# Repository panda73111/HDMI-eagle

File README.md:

[pandaLight on 3D Warehouse](https://3dwarehouse.sketchup.com/model.html?id=u218e26f0-69cc-4069-a915-63719f472bee)

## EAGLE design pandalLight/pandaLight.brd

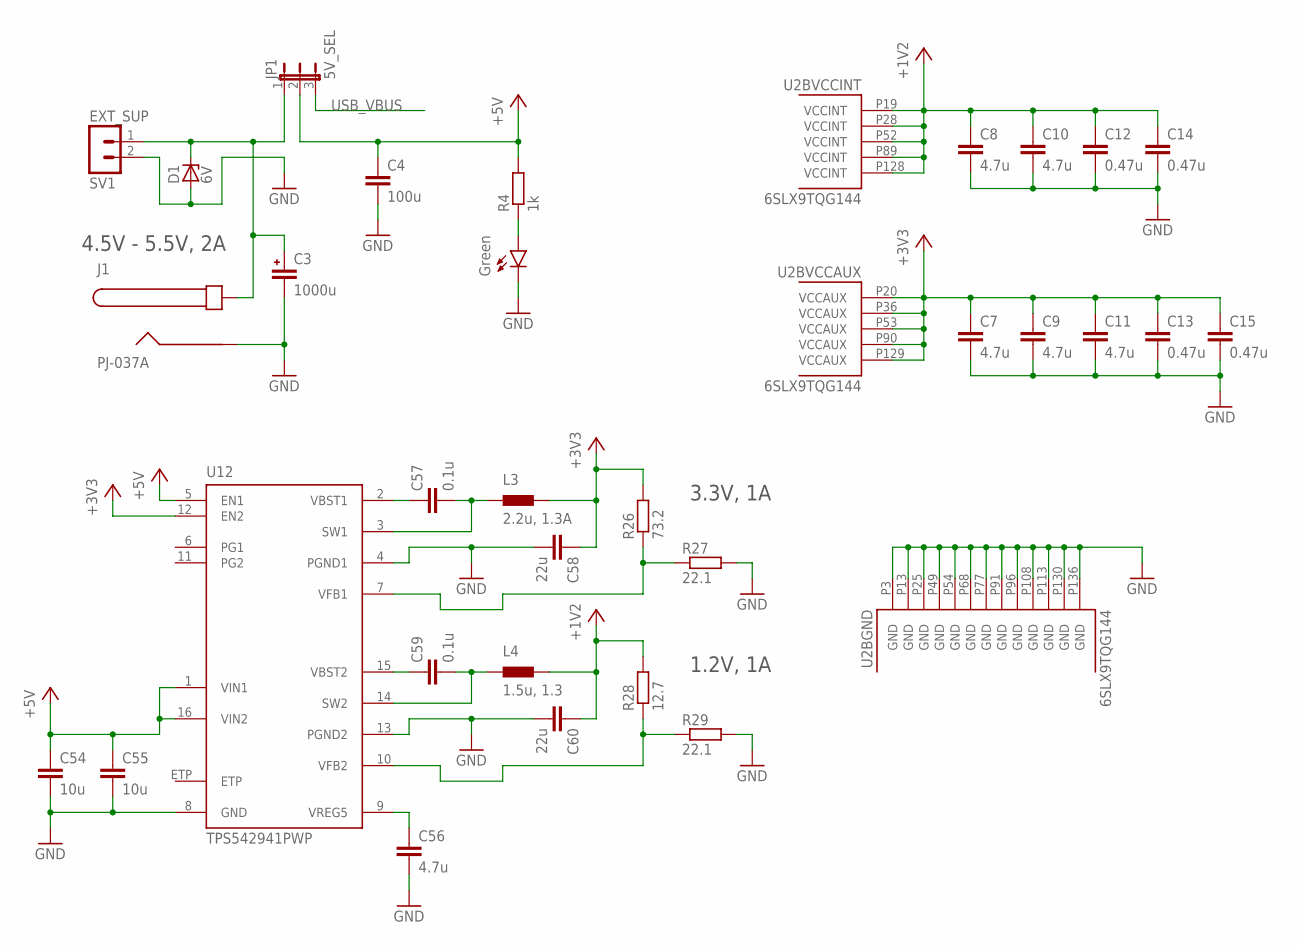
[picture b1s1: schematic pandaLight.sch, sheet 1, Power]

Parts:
C3: 1000u; MVY_HA0; PARTNO EMVY6R3ADA102MHA0G
C4: 100u; C1206; PARTNO CL31A107MQHNNNE
C7, C8, C9, C10, C11, C56: 4.7u; C0603; PARTNO C0603C475K9PACTU
C12, C13, C14, C15: 0.47u; C0402; PARTNO C1005X5R0J474K050BB
C54, C55: 10u; C0603; PARTNO CL10A106MQ8NNNC
C57, C59: 0.1u; C0402; PARTNO CL05B104KP5NNNC
C58, C60: 22u; C0603; PARTNO CL10A226MQ8NRNC
D1: 6V; DO-214AC; PARTNO SMAJ6.0A
J1: PJ-037A; PARTNO PJ-037A
JP1: 5V_SEL; JP2; PARTNO SPC02SYAN
L3: 2.2u, 1.3A; SRN3015_3X3; PARTNO SRN3015-2R2M
L4: 1.5u, 1.3; SRN3015_3X3; PARTNO SRN3015-1R5Y
LED1: Green; LED-0603; PARTNO LTST-C191KGKT
R4: 1k; R0402; PARTNO ERJ-2RKF1001X
R26: 73.2; R0402; PARTNO ERJ-2RKF73R2X
R27, R29: 22.1; R0402; PARTNO ERJ-2RKF22R1X
R28: 12.7; R0402; PARTNO ERJ-2RKF12R7X
SV1: EXT_SUP; MA02-1; PARTNO *
U2: 6SLX9TQG144; TQ144; PARTNO XC6SLX9-3TQG144C
U12: TPS542941PWP; R-PDSO-G16; PARTNO TPS542941PWP

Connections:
5V_SUP: C3.1, D1.C, J1.CENTER, JP1.1, SV1.1; also elsewhere on the board
+1V2: C8.1, C10.1, C12.1, C14.1, C60.1, L4.2, R28.2, U2.P19 (VCCINT), U2.P28 (VCCINT), U2.P52 (VCCINT), U2.P89 (VCCINT), U2.P128 (VCCINT)
+3V3: C7.1, C9.1, C11.1, C13.1, C15.1, C58.1, L3.2, R26.2, U2.P20 (VCCAUX), U2.P36 (VCCAUX), U2.P53 (VCCAUX), U2.P90 (VCCAUX), U2.P129 (VCCAUX), U12.12 (EN2); also elsewhere on the board
+5V: C4.1, C54.1, C55.1, JP1.2, R4.2, U12.1 (VIN1), U12.5 (EN1), U12.16 (VIN2); also elsewhere on the board
GND: C3.2, C4.2, C7.2, C8.2, C9.2, C10.2, C11.2, C12.2, C13.2, C14.2, C15.2, C54.2, C55.2, C56.2, C58.2, C60.2, D1.A, J1.BARREL, LED1.C, R27.2, R29.2, SV1.2, U2.P3 (GND), U2.P13 (GND), U2.P25 (GND), U2.P49 (GND), U2.P54 (GND), U2.P68 (GND), U2.P77 (GND), U2.P91 (GND), U2.P96 (GND), U2.P108 (GND), U2.P113 (GND), U2.P130 (GND), U2.P136 (GND), U12.4 (PGND1), U12.8 (GND), U12.13 (PGND2); also elsewhere on the board
unnamed: C57.2, L3.1, U12.3 (SW1)
unnamed: R26.1, R27.1, U12.7 (VFB1)
unnamed: C57.1, U12.2 (VBST1)
unnamed: R28.1, R29.1, U12.10 (VFB2)
unnamed: C59.1, U12.15 (VBST2)
unnamed: C59.2, L4.1, U12.14 (SW2)
unnamed: LED1.A, R4.1
USB_VBUS: JP1.3; also elsewhere on the board
VREG5: C56.1, U12.9 (VREG5)

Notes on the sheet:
4.5V - 5.5V, 2A
3.3V, 1A
1.2V, 1A

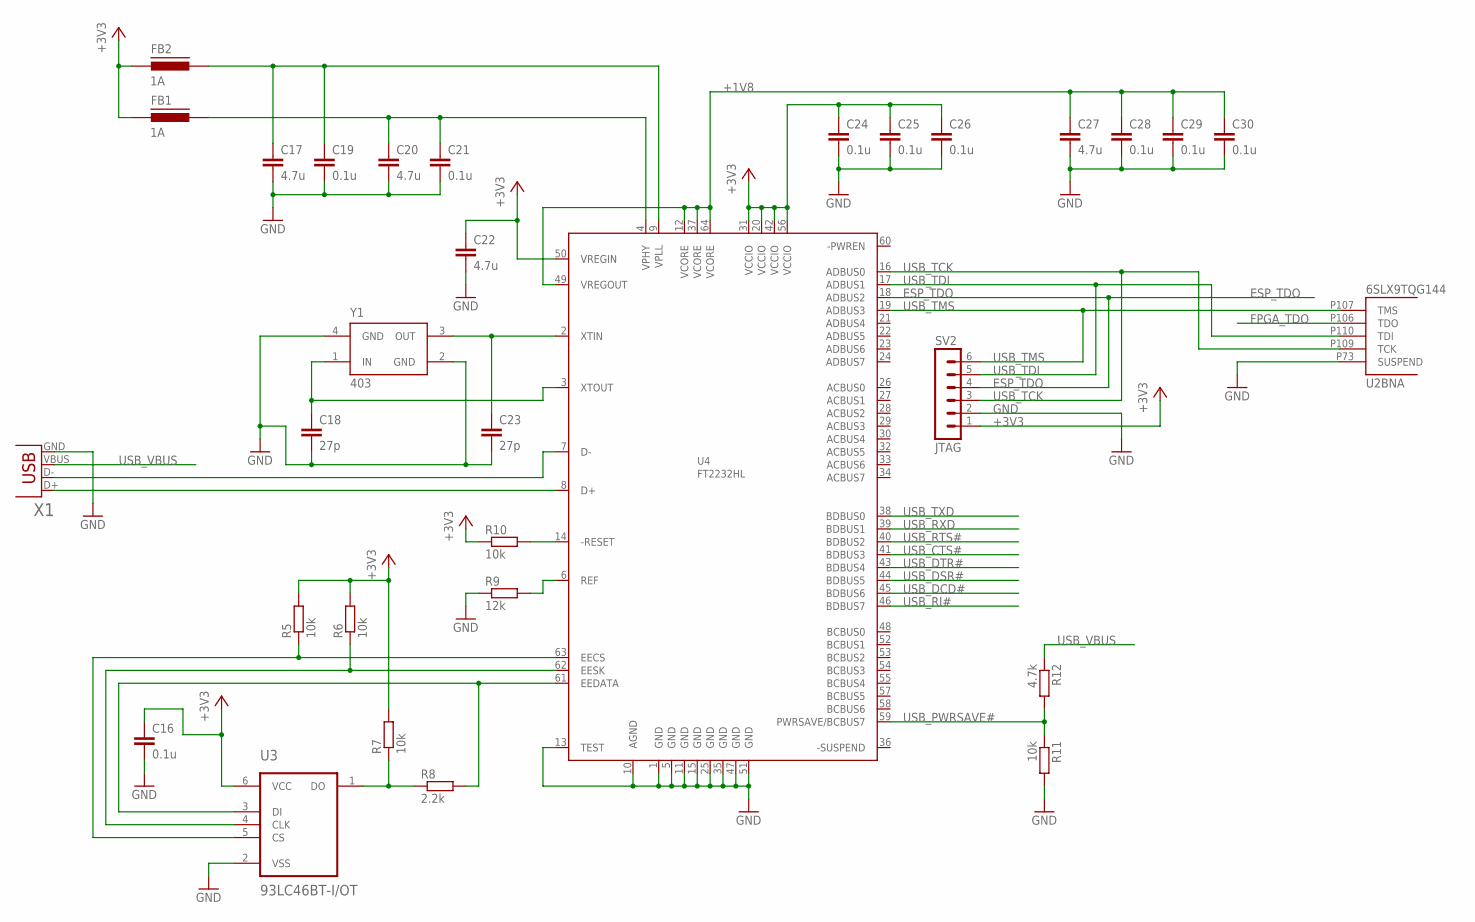
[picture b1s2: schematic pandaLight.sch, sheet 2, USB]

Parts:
C16, C19, C21, C24, C25, C26, C28, C29, C30: 0.1u; C0402; PARTNO CL05B104KP5NNNC
C17, C20, C22, C27: 4.7u; C0603; PARTNO C0603C475K9PACTU
C18, C23: 27p; C0402; PARTNO CL05C270JB5NNNC
FB1, FB2: 1A; FB0402; PARTNO BK1005HS100-T
R5, R6, R7, R10, R11: 10k; R0402; PARTNO ERJ-2RKF1002X
R8: 2.2k; R0402; PARTNO ERJ-2RKF2201X
R9: 12k; R0402; PARTNO ERJ-2RKF1202X
R12: 4.7k; R0402; PARTNO ERJ-2RKF4701X
SV2: JTAG; MA06-1; PARTNO *
U2: 6SLX9TQG144; TQ144; PARTNO XC6SLX9-3TQG144C
U3: 93LC46BT-I/OT; SOT23-6; PARTNO 93LC46BT-I/OT
U4: FT2232HL; LQFP64; PARTNO FT2232HL-REEL
X1: USBUB-S; USB-UB-S; PARTNO 10118192-0001LF
Y1: 403; 403-3.2X2.5; PARTNO 403C35D12M00000

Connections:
+1V8: C27.1, C28.1, C29.1, C30.1, U4.12 (VCORE), U4.37 (VCORE), U4.49 (VREGOUT), U4.64 (VCORE)
+3V3: C16.1, C22.1, C24.1, C25.1, C26.1, FB1.1, FB2.1, R5.2, R6.2, R7.2, R10.1, SV2.1, U3.6 (VCC), U4.20 (VCCIO), U4.31 (VCCIO), U4.42 (VCCIO), U4.50 (VREGIN), U4.56 (VCCIO); also elsewhere on the board
ESP_TDO: SV2.4, U4.18 (ADBUS2); also elsewhere on the board
FPGA_TDO: U2.P106 (TDO); also elsewhere on the board
GND: C16.2, C17.2, C18.2, C19.2, C20.2, C21.2, C22.2, C23.2, C24.2, C25.2, C26.2, C27.2, C28.2, C29.2, C30.2, R9.1, R11.2, SV2.2, U2.P73 (SUSPEND), U3.2 (VSS), U4.1 (GND), U4.5 (GND), U4.10 (AGND), U4.11 (GND), U4.13 (TEST), U4.15 (GND), U4.25 (GND), U4.35 (GND), U4.47 (GND), U4.51 (GND), X1.GND, Y1.2 (GND), Y1.4 (GND); also elsewhere on the board
unnamed: C23.1, U4.2 (XTIN), Y1.3 (OUT)
unnamed: C18.1, U4.3 (XTOUT), Y1.1 (IN)
unnamed: R5.1, U3.5 (CS), U4.63 (EECS)
unnamed: U4.7 (D-), X1.D-
unnamed: U4.8 (D+), X1.D+
unnamed: R6.1, U3.4 (CLK), U4.62 (EESK)
unnamed: R8.2, U3.3 (DI), U4.61 (EEDATA)
unnamed: R9.2, U4.6 (REF)
unnamed: R7.1, R8.1, U3.1 (DO)
unnamed: R10.2, U4.14 (-RESET)
unnamed: C20.1, C21.1, FB1.2, U4.4 (VPHY)
unnamed: C17.1, C19.1, FB2.2, U4.9 (VPLL)
USB_CTS#: U4.41 (BDBUS3); also elsewhere on the board
USB_DCD#: U4.45 (BDBUS6); also elsewhere on the board
USB_DSR#: U4.44 (BDBUS5); also elsewhere on the board
USB_DTR#: U4.43 (BDBUS4); also elsewhere on the board
USB_PWRSAVE#: R11.1, R12.2, U4.59 (PWRSAVE/BCBUS7)
USB_RI#: U4.46 (BDBUS7); also elsewhere on the board
USB_RTS#: U4.40 (BDBUS2); also elsewhere on the board
USB_RXD: U4.39 (BDBUS1); also elsewhere on the board
USB_TCK: SV2.3, U2.P109 (TCK), U4.16 (ADBUS0); also elsewhere on the board
USB_TDI: SV2.5, U2.P110 (TDI), U4.17 (ADBUS1)
USB_TMS: SV2.6, U2.P107 (TMS), U4.19 (ADBUS3); also elsewhere on the board
USB_TXD: U4.38 (BDBUS0); also elsewhere on the board
USB_VBUS: R12.1, X1.VBUS; also elsewhere on the board

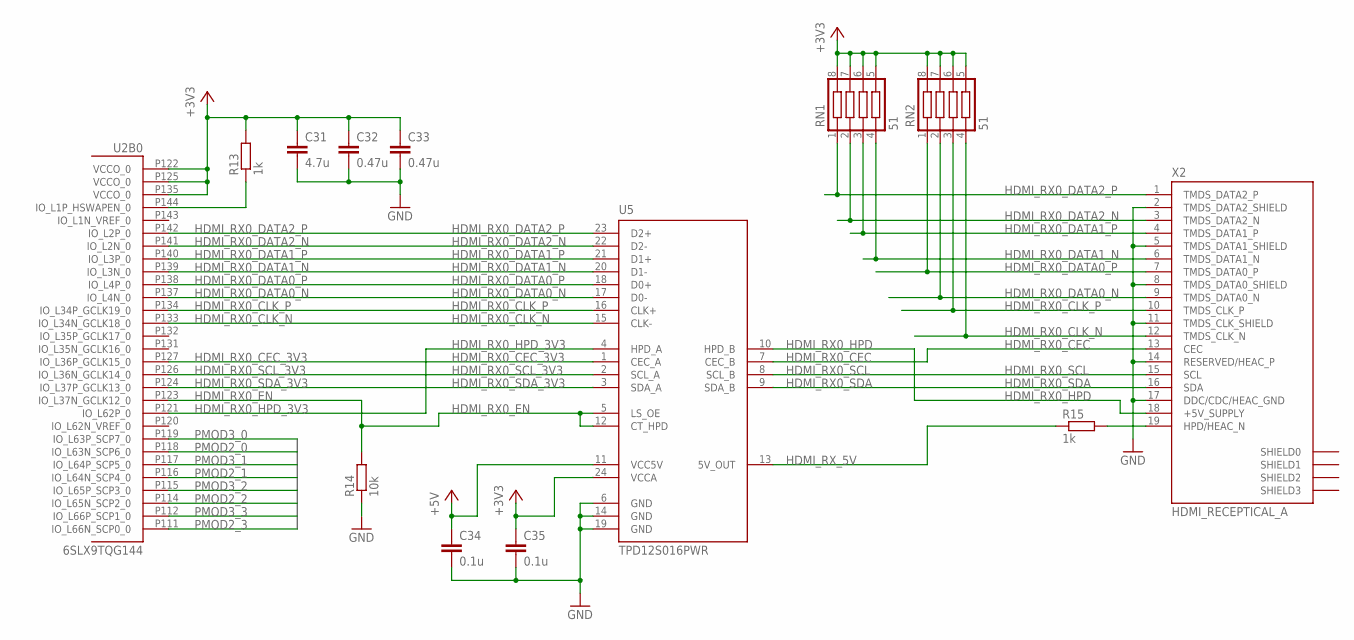
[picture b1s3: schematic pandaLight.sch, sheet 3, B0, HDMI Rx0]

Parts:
C31: 4.7u; C0603; PARTNO C0603C475K9PACTU
C32, C33: 0.47u; C0402; PARTNO C1005X5R0J474K050BB
C34, C35: 0.1u; C0402; PARTNO CL05B104KP5NNNC
R13, R15: 1k; R0402; PARTNO ERJ-2RKF1001X
R14: 10k; R0402; PARTNO ERJ-2RKF1002X
RN1, RN2: 51; 741C083; PARTNO 741C083510JP
U2: 6SLX9TQG144; TQ144; PARTNO XC6SLX9-3TQG144C
U5: TPD12S016PWR; PW_R-PDSO-G24; PARTNO TPD12S016PWR
X2: HDMI_RECEPTICAL_A; HDMI_TYPE_A_RECEPTICAL; PARTNO 10029449-111RLF

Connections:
+3V3: C31.1, C32.1, C33.1, C35.1, R13.2, RN1.5, RN1.6, RN1.7, RN1.8, RN2.5, RN2.6, RN2.7, RN2.8, U2.P122 (VCCO_0), U2.P125 (VCCO_0), U2.P135 (VCCO_0), U5.24 (VCCA); also elsewhere on the board
+5V: C34.1, U5.11 (VCC5V); also elsewhere on the board
GND: C31.2, C32.2, C33.2, C34.2, C35.2, R14.1, U5.6 (GND), U5.14 (GND), U5.19 (GND), X2.2 (TMDS_DATA2_SHIELD), X2.5 (TMDS_DATA1_SHIELD), X2.8 (TMDS_DATA0_SHIELD), X2.11 (TMDS_CLK_SHIELD), X2.14 (RESERVED/HEAC_P), X2.17 (DDC/CDC/HEAC_GND); also elsewhere on the board
HDMI_RX0_CEC: U5.7 (CEC_B), X2.13 (CEC)
HDMI_RX0_CEC_3V3: U2.P127 (IO_L36P_GCLK15_0), U5.1 (CEC_A)
HDMI_RX0_CLK_N: RN2.4, U2.P133 (IO_L34N_GCLK18_0), U5.15 (CLK-), X2.12 (TMDS_CLK_N)
HDMI_RX0_CLK_P: RN2.3, U2.P134 (IO_L34P_GCLK19_0), U5.16 (CLK+), X2.10 (TMDS_CLK_P)
HDMI_RX0_DATA0_N: RN2.2, U2.P137 (IO_L4N_0), U5.17 (D0-), X2.9 (TMDS_DATA0_N)
HDMI_RX0_DATA0_P: RN2.1, U2.P138 (IO_L4P_0), U5.18 (D0+), X2.7 (TMDS_DATA0_P)
HDMI_RX0_DATA1_N: RN1.4, U2.P139 (IO_L3N_0), U5.20 (D1-), X2.6 (TMDS_DATA1_N)
HDMI_RX0_DATA1_P: RN1.3, U2.P140 (IO_L3P_0), U5.21 (D1+), X2.4 (TMDS_DATA1_P)
HDMI_RX0_DATA2_N: RN1.2, U2.P141 (IO_L2N_0), U5.22 (D2-), X2.3 (TMDS_DATA2_N)
HDMI_RX0_DATA2_P: RN1.1, U2.P142 (IO_L2P_0), U5.23 (D2+), X2.1 (TMDS_DATA2_P)
HDMI_RX0_EN: R14.2, U2.P123 (IO_L37N_GCLK12_0), U5.5 (LS_OE), U5.12 (CT_HPD)
HDMI_RX0_HPD: U5.10 (HPD_B), X2.18 (+5V_SUPPLY)
HDMI_RX0_HPD_3V3: U2.P121 (IO_L62P_0), U5.4 (HPD_A)
HDMI_RX0_SCL: U5.8 (SCL_B), X2.15 (SCL)
HDMI_RX0_SCL_3V3: U2.P126 (IO_L36N_GCLK14_0), U5.2 (SCL_A)
HDMI_RX0_SDA: U5.9 (SDA_B), X2.16 (SDA)
HDMI_RX0_SDA_3V3: U2.P124 (IO_L37P_GCLK13_0), U5.3 (SDA_A)
HDMI_RX_5V: R15.1, U5.13 (5V_OUT)
unnamed: R13.1, U2.P144 (IO_L1P_HSWAPEN_0)
unnamed: R15.2, X2.19 (HPD/HEAC_N)
PMOD2_0: U2.P118 (IO_L63N_SCP6_0); also elsewhere on the board
PMOD2_1: U2.P116 (IO_L64N_SCP4_0); also elsewhere on the board
PMOD2_2: U2.P114 (IO_L65N_SCP2_0); also elsewhere on the board
PMOD2_3: U2.P111 (IO_L66N_SCP0_0); also elsewhere on the board
PMOD3_0: U2.P119 (IO_L63P_SCP7_0); also elsewhere on the board
PMOD3_1: U2.P117 (IO_L64P_SCP5_0); also elsewhere on the board
PMOD3_2: U2.P115 (IO_L65P_SCP3_0); also elsewhere on the board
PMOD3_3: U2.P112 (IO_L66P_SCP1_0); also elsewhere on the board

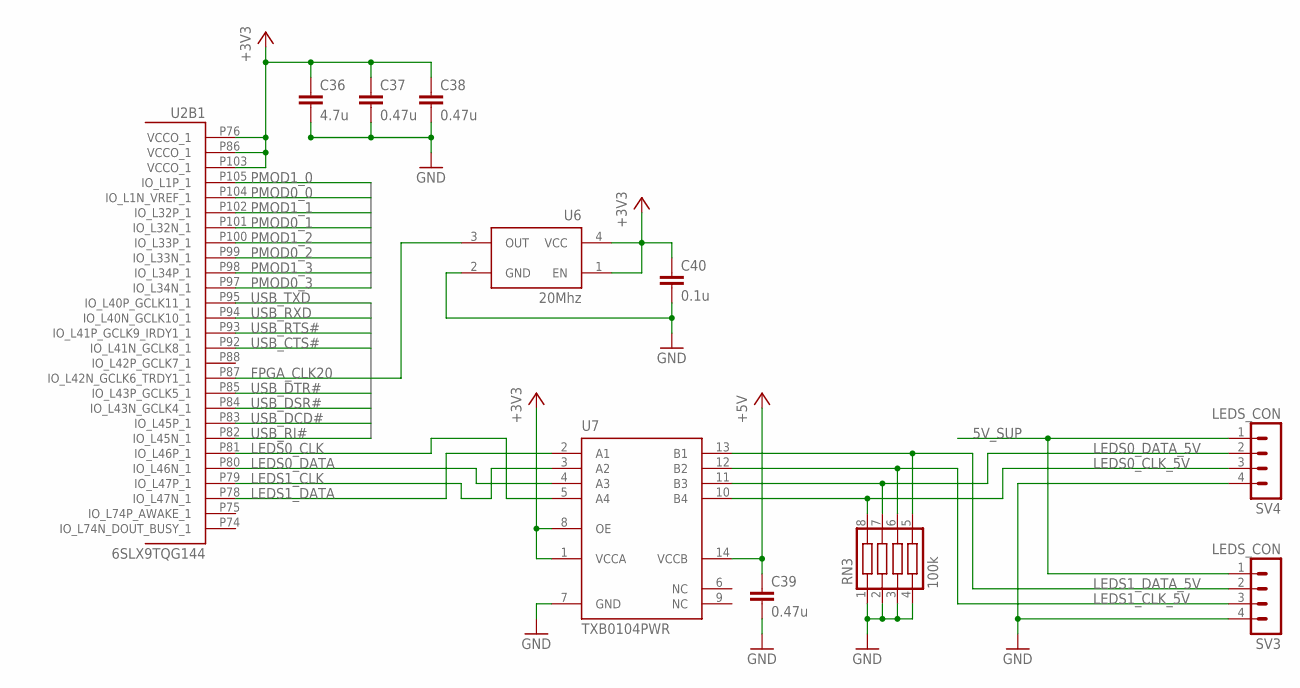
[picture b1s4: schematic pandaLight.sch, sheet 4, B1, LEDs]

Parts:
C36: 4.7u; C0603; PARTNO C0603C475K9PACTU
C37, C38, C39: 0.47u; C0402; PARTNO C1005X5R0J474K050BB
C40: 0.1u; C0402; PARTNO CL05B104KP5NNNC
RN3: 100k; 741C083; PARTNO 741C083104JP
SV3, SV4: LEDS_CON; MA04-1; PARTNO *
U2: 6SLX9TQG144; TQ144; PARTNO XC6SLX9-3TQG144C
U6: 20Mhz; OSCI-1.6X1.2; PARTNO ASCO-20.000MHZ-EK-T3
U7: TXB0104PWR; R-PDSO-G14; PARTNO TXB0104PWR

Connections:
5V_SUP: SV3.1, SV4.1; also elsewhere on the board
+3V3: C36.1, C37.1, C38.1, C40.1, U2.P76 (VCCO_1), U2.P86 (VCCO_1), U2.P103 (VCCO_1), U6.1 (EN), U6.4 (VCC), U7.1 (VCCA), U7.8 (OE); also elsewhere on the board
+5V: C39.1, U7.14 (VCCB); also elsewhere on the board
FPGA_CLK20: U2.P87 (IO_L42N_GCLK6_TRDY1_1), U6.3 (OUT)
GND: C36.2, C37.2, C38.2, C39.2, C40.2, RN3.1, RN3.2, RN3.3, RN3.4, SV3.4, SV4.4, U6.2 (GND), U7.7 (GND); also elsewhere on the board
LEDS0_CLK: U2.P81 (IO_L46P_1), U7.5 (A4)
LEDS0_CLK_5V: RN3.8, SV4.3, U7.10 (B4)
LEDS0_DATA: U2.P80 (IO_L46N_1), U7.4 (A3)
LEDS0_DATA_5V: RN3.7, SV4.2, U7.11 (B3)
LEDS1_CLK: U2.P79 (IO_L47P_1), U7.3 (A2)
LEDS1_CLK_5V: RN3.6, SV3.3, U7.12 (B2)
LEDS1_DATA: U2.P78 (IO_L47N_1), U7.2 (A1)
LEDS1_DATA_5V: RN3.5, SV3.2, U7.13 (B1)
PMOD0_0: U2.P104 (IO_L1N_VREF_1); also elsewhere on the board
PMOD0_1: U2.P101 (IO_L32N_1); also elsewhere on the board
PMOD0_2: U2.P99 (IO_L33N_1); also elsewhere on the board
PMOD0_3: U2.P97 (IO_L34N_1); also elsewhere on the board
PMOD1_0: U2.P105 (IO_L1P_1); also elsewhere on the board
PMOD1_1: U2.P102 (IO_L32P_1); also elsewhere on the board
PMOD1_2: U2.P100 (IO_L33P_1); also elsewhere on the board
PMOD1_3: U2.P98 (IO_L34P_1); also elsewhere on the board
USB_CTS#: U2.P92 (IO_L41N_GCLK8_1); also elsewhere on the board
USB_DCD#: U2.P83 (IO_L45P_1); also elsewhere on the board
USB_DSR#: U2.P84 (IO_L43N_GCLK4_1); also elsewhere on the board
USB_DTR#: U2.P85 (IO_L43P_GCLK5_1); also elsewhere on the board
USB_RI#: U2.P82 (IO_L45N_1); also elsewhere on the board
USB_RTS#: U2.P93 (IO_L41P_GCLK9_IRDY1_1); also elsewhere on the board
USB_RXD: U2.P94 (IO_L40N_GCLK10_1); also elsewhere on the board
USB_TXD: U2.P95 (IO_L40P_GCLK11_1); also elsewhere on the board

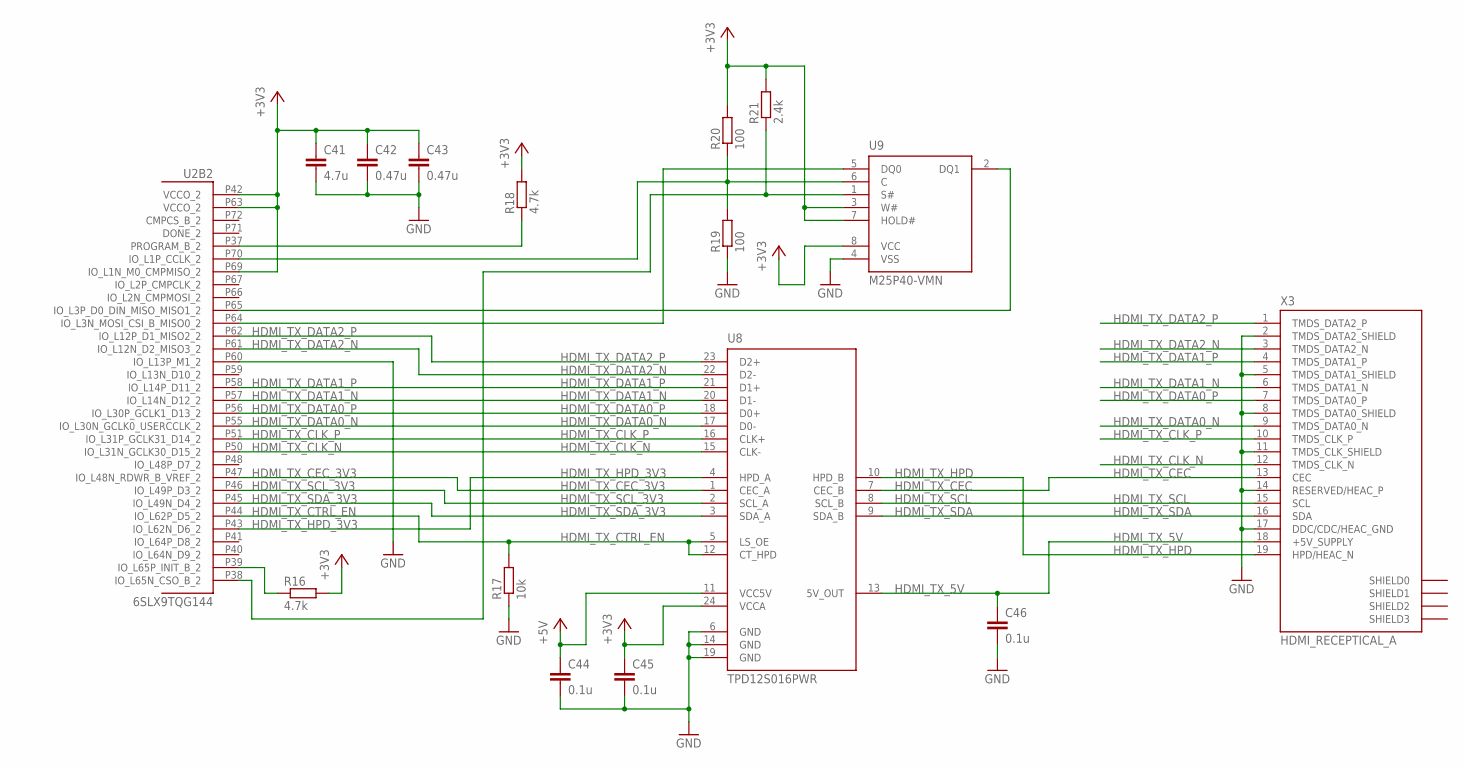
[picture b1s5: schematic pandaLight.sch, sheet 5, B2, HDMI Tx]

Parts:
C41: 4.7u; C0603; PARTNO C0603C475K9PACTU
C42, C43: 0.47u; C0402; PARTNO C1005X5R0J474K050BB
C44, C45, C46: 0.1u; C0402; PARTNO CL05B104KP5NNNC
R16, R18: 4.7k; R0402; PARTNO ERJ-2RKF4701X
R17: 10k; R0402; PARTNO ERJ-2RKF1002X
R19, R20: 100; R0402; PARTNO ERJ-2GEJ101X
R21: 2.4k; R0402; PARTNO ERJ-2RKF2401X
U2: 6SLX9TQG144; TQ144; PARTNO XC6SLX9-3TQG144C
U8: TPD12S016PWR; PW_R-PDSO-G24; PARTNO TPD12S016PWR
U9: M25P40-VMN; SO8N; PARTNO M25P80-VMN6TP
X3: HDMI_RECEPTICAL_A; HDMI_TYPE_A_RECEPTICAL; PARTNO 10029449-111RLF

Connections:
+3V3: C41.1, C42.1, C43.1, C45.1, R16.2, R18.2, R20.2, R21.2, U2.P42 (VCCO_2), U2.P63 (VCCO_2), U2.P69 (IO_L1N_M0_CMPMISO_2), U8.24 (VCCA), U9.3 (W#), U9.7 (HOLD#), U9.8 (VCC); also elsewhere on the board
+5V: C44.1, U8.11 (VCC5V); also elsewhere on the board
GND: C41.2, C42.2, C43.2, C44.2, C45.2, C46.2, R17.1, R19.1, U2.P60 (IO_L13P_M1_2), U8.6 (GND), U8.14 (GND), U8.19 (GND), U9.4 (VSS), X3.2 (TMDS_DATA2_SHIELD), X3.5 (TMDS_DATA1_SHIELD), X3.8 (TMDS_DATA0_SHIELD), X3.11 (TMDS_CLK_SHIELD), X3.14 (RESERVED/HEAC_P), X3.17 (DDC/CDC/HEAC_GND); also elsewhere on the board
HDMI_TX_5V: C46.1, U8.13 (5V_OUT), X3.18 (+5V_SUPPLY)
HDMI_TX_CEC: U8.7 (CEC_B), X3.13 (CEC)
HDMI_TX_CEC_3V3: U2.P47 (IO_L48N_RDWR_B_VREF_2), U8.1 (CEC_A)
HDMI_TX_CLK_N: U2.P50 (IO_L31N_GCLK30_D15_2), U8.15 (CLK-), X3.12 (TMDS_CLK_N)
HDMI_TX_CLK_P: U2.P51 (IO_L31P_GCLK31_D14_2), U8.16 (CLK+), X3.10 (TMDS_CLK_P)
HDMI_TX_CTRL_EN: R17.2, U2.P44 (IO_L62P_D5_2), U8.5 (LS_OE), U8.12 (CT_HPD)
HDMI_TX_DATA0_N: U2.P55 (IO_L30N_GCLK0_USERCCLK_2), U8.17 (D0-), X3.9 (TMDS_DATA0_N)
HDMI_TX_DATA0_P: U2.P56 (IO_L30P_GCLK1_D13_2), U8.18 (D0+), X3.7 (TMDS_DATA0_P)
HDMI_TX_DATA1_N: U2.P57 (IO_L14N_D12_2), U8.20 (D1-), X3.6 (TMDS_DATA1_N)
HDMI_TX_DATA1_P: U2.P58 (IO_L14P_D11_2), U8.21 (D1+), X3.4 (TMDS_DATA1_P)
HDMI_TX_DATA2_N: U2.P61 (IO_L12N_D2_MISO3_2), U8.22 (D2-), X3.3 (TMDS_DATA2_N)
HDMI_TX_DATA2_P: U2.P62 (IO_L12P_D1_MISO2_2), U8.23 (D2+), X3.1 (TMDS_DATA2_P)
HDMI_TX_HPD: U8.10 (HPD_B), X3.19 (HPD/HEAC_N)
HDMI_TX_HPD_3V3: U2.P43 (IO_L62N_D6_2), U8.4 (HPD_A)
HDMI_TX_SCL: U8.8 (SCL_B), X3.15 (SCL)
HDMI_TX_SCL_3V3: U2.P46 (IO_L49P_D3_2), U8.2 (SCL_A)
HDMI_TX_SDA: U8.9 (SDA_B), X3.16 (SDA)
HDMI_TX_SDA_3V3: U2.P45 (IO_L49N_D4_2), U8.3 (SDA_A)
unnamed: R18.1, U2.P37 (PROGRAM_B_2)
unnamed: R16.1, U2.P39 (IO_L65P_INIT_B_2)
unnamed: U2.P64 (IO_L3N_MOSI_CSI_B_MISO0_2), U9.5 (DQ0)
unnamed: R21.1, U2.P38 (IO_L65N_CSO_B_2), U9.1 (S#)
unnamed: R19.2, R20.1, U2.P70 (IO_L1P_CCLK_2), U9.6 (C)
unnamed: U2.P65 (IO_L3P_D0_DIN_MISO_MISO1_2), U9.2 (DQ1)

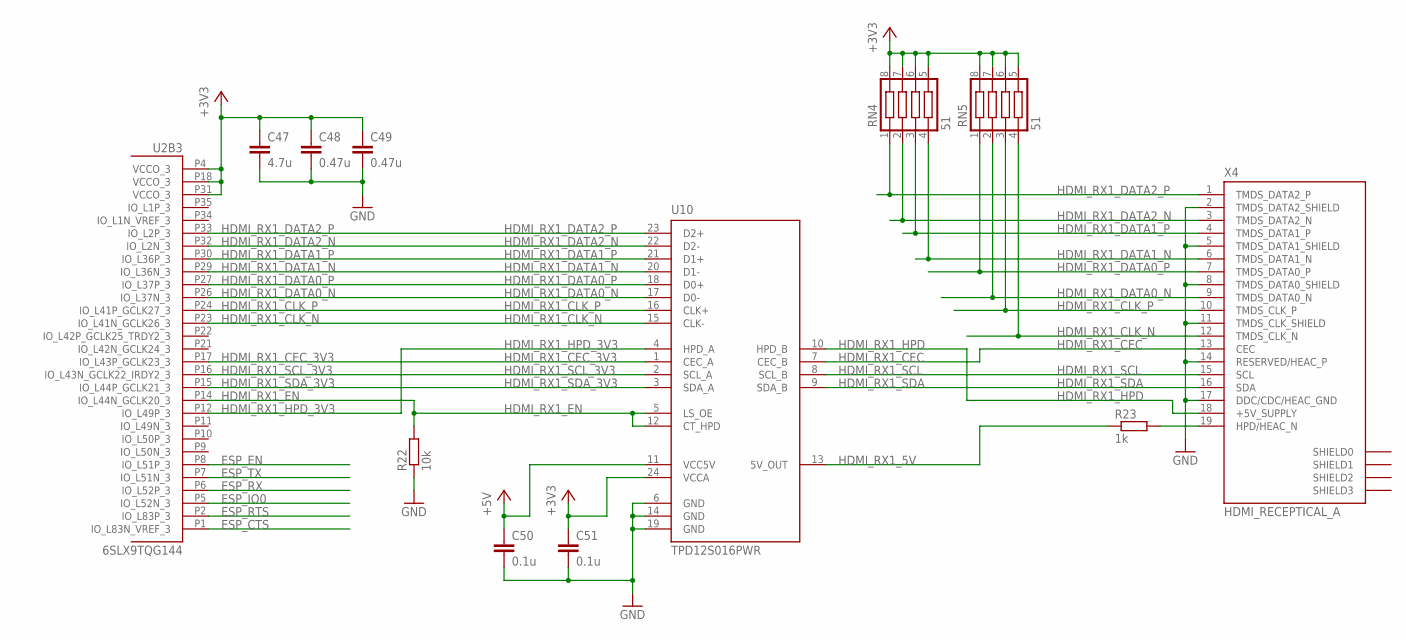
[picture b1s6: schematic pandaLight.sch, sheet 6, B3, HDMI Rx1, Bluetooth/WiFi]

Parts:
C47: 4.7u; C0603; PARTNO C0603C475K9PACTU
C48, C49: 0.47u; C0402; PARTNO C1005X5R0J474K050BB
C50, C51: 0.1u; C0402; PARTNO CL05B104KP5NNNC
R22: 10k; R0402; PARTNO ERJ-2RKF1002X
R23: 1k; R0402; PARTNO ERJ-2RKF1001X
RN4, RN5: 51; 741C083; PARTNO 741C083510JP
U2: 6SLX9TQG144; TQ144; PARTNO XC6SLX9-3TQG144C
U10: TPD12S016PWR; PW_R-PDSO-G24; PARTNO TPD12S016PWR
X4: HDMI_RECEPTICAL_A; HDMI_TYPE_A_RECEPTICAL; PARTNO 10029449-111RLF

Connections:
+3V3: C47.1, C48.1, C49.1, C51.1, RN4.5, RN4.6, RN4.7, RN4.8, RN5.5, RN5.6, RN5.7, RN5.8, U2.P4 (VCCO_3), U2.P18 (VCCO_3), U2.P31 (VCCO_3), U10.24 (VCCA); also elsewhere on the board
+5V: C50.1, U10.11 (VCC5V); also elsewhere on the board
ESP_CTS: U2.P1 (IO_L83N_VREF_3); also elsewhere on the board
ESP_EN: U2.P8 (IO_L51P_3); also elsewhere on the board
ESP_IO0: U2.P5 (IO_L52N_3); also elsewhere on the board
ESP_RTS: U2.P2 (IO_L83P_3); also elsewhere on the board
ESP_RX: U2.P6 (IO_L52P_3); also elsewhere on the board
ESP_TX: U2.P7 (IO_L51N_3); also elsewhere on the board
GND: C47.2, C48.2, C49.2, C50.2, C51.2, R22.1, U10.6 (GND), U10.14 (GND), U10.19 (GND), X4.2 (TMDS_DATA2_SHIELD), X4.5 (TMDS_DATA1_SHIELD), X4.8 (TMDS_DATA0_SHIELD), X4.11 (TMDS_CLK_SHIELD), X4.14 (RESERVED/HEAC_P), X4.17 (DDC/CDC/HEAC_GND); also elsewhere on the board
HDMI_RX1_5V: R23.1, U10.13 (5V_OUT)
HDMI_RX1_CEC: U10.7 (CEC_B), X4.13 (CEC)
HDMI_RX1_CEC_3V3: U2.P17 (IO_L43P_GCLK23_3), U10.1 (CEC_A)
HDMI_RX1_CLK_N: RN5.4, U2.P23 (IO_L41N_GCLK26_3), U10.15 (CLK-), X4.12 (TMDS_CLK_N)
HDMI_RX1_CLK_P: RN5.3, U2.P24 (IO_L41P_GCLK27_3), U10.16 (CLK+), X4.10 (TMDS_CLK_P)
HDMI_RX1_DATA0_N: RN5.2, U2.P26 (IO_L37N_3), U10.17 (D0-), X4.9 (TMDS_DATA0_N)
HDMI_RX1_DATA0_P: RN5.1, U2.P27 (IO_L37P_3), U10.18 (D0+), X4.7 (TMDS_DATA0_P)
HDMI_RX1_DATA1_N: RN4.4, U2.P29 (IO_L36N_3), U10.20 (D1-), X4.6 (TMDS_DATA1_N)
HDMI_RX1_DATA1_P: RN4.3, U2.P30 (IO_L36P_3), U10.21 (D1+), X4.4 (TMDS_DATA1_P)
HDMI_RX1_DATA2_N: RN4.2, U2.P32 (IO_L2N_3), U10.22 (D2-), X4.3 (TMDS_DATA2_N)
HDMI_RX1_DATA2_P: RN4.1, U2.P33 (IO_L2P_3), U10.23 (D2+), X4.1 (TMDS_DATA2_P)
HDMI_RX1_EN: R22.2, U2.P14 (IO_L44N_GCLK20_3), U10.5 (LS_OE), U10.12 (CT_HPD)
HDMI_RX1_HPD: U10.10 (HPD_B), X4.18 (+5V_SUPPLY)
HDMI_RX1_HPD_3V3: U2.P12 (IO_L49P_3), U10.4 (HPD_A)
HDMI_RX1_SCL: U10.8 (SCL_B), X4.15 (SCL)
HDMI_RX1_SCL_3V3: U2.P16 (IO_L43N_GCLK22_IRDY2_3), U10.2 (SCL_A)
HDMI_RX1_SDA: U10.9 (SDA_B), X4.16 (SDA)
HDMI_RX1_SDA_3V3: U2.P15 (IO_L44P_GCLK21_3), U10.3 (SDA_A)
unnamed: R23.2, X4.19 (HPD/HEAC_N)

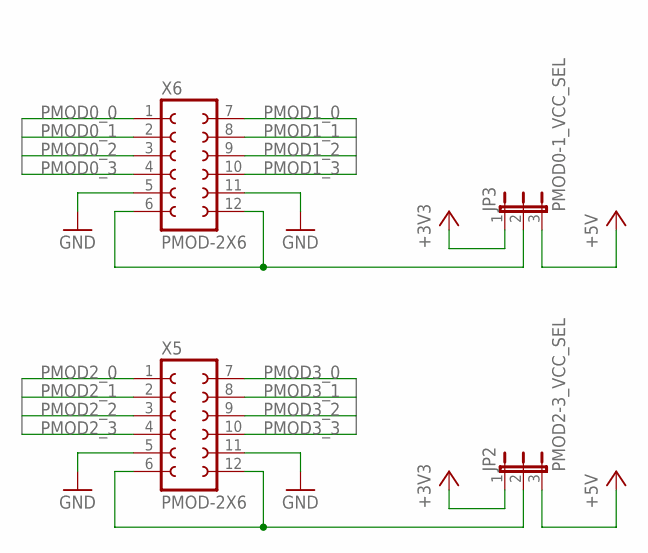
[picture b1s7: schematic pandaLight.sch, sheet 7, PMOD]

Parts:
JP2: PMOD2-3_VCC_SEL; JP2; PARTNO SPC02SYAN
JP3: PMOD0-1_VCC_SEL; JP2; PARTNO SPC02SYAN
X5, X6: PMOD-2X6; PARTNO PPTC062LJBN-RC

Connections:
+3V3: JP2.1, JP3.1; also elsewhere on the board
+5V: JP2.3, JP3.3; also elsewhere on the board
GND: X5.5, X5.11, X6.5, X6.11; also elsewhere on the board
unnamed: JP2.2, X5.6, X5.12
unnamed: JP3.2, X6.6, X6.12
PMOD0_0: X6.1; also elsewhere on the board
PMOD0_1: X6.2; also elsewhere on the board
PMOD0_2: X6.3; also elsewhere on the board
PMOD0_3: X6.4; also elsewhere on the board
PMOD1_0: X6.7; also elsewhere on the board
PMOD1_1: X6.8; also elsewhere on the board
PMOD1_2: X6.9; also elsewhere on the board
PMOD1_3: X6.10; also elsewhere on the board
PMOD2_0: X5.1; also elsewhere on the board
PMOD2_1: X5.2; also elsewhere on the board
PMOD2_2: X5.3; also elsewhere on the board
PMOD2_3: X5.4; also elsewhere on the board
PMOD3_0: X5.7; also elsewhere on the board
PMOD3_1: X5.8; also elsewhere on the board
PMOD3_2: X5.9; also elsewhere on the board
PMOD3_3: X5.10; also elsewhere on the board

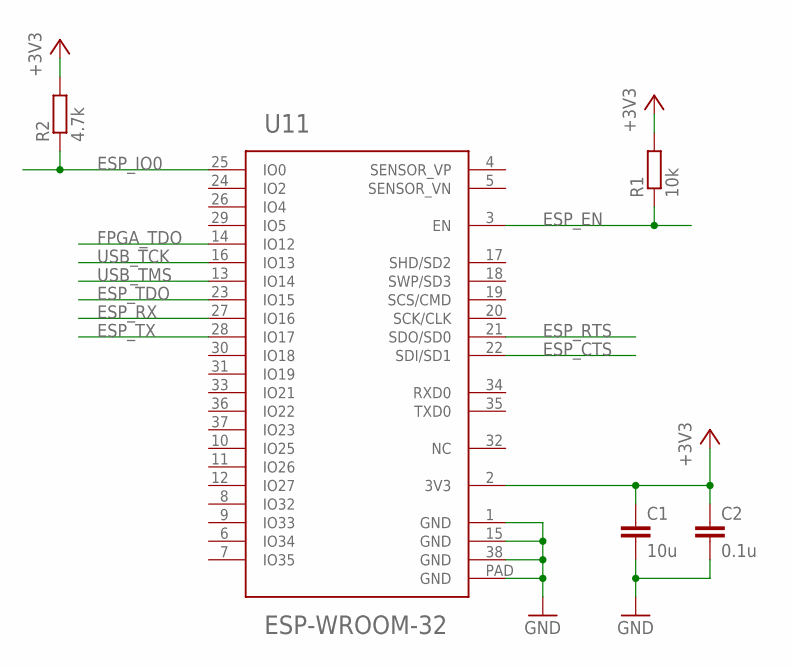
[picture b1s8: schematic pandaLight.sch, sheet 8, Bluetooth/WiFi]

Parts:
C1: 10u; C0603
C2: 0.1u; C0402; PARTNO CL05B104KP5NNNC
R1: 10k; R0402; PARTNO ERJ-2RKF1002X
R2: 4.7k; R0402; PARTNO ERJ-2RKF1002X
U11: ESP-WROOM-32

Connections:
+3V3: C1.1, C2.1, R1.2, R2.2, U11.2 (3V3); also elsewhere on the board
ESP_CTS: U11.22 (SDI/SD1); also elsewhere on the board
ESP_EN: R1.1, U11.3 (EN); also elsewhere on the board
ESP_IO0: R2.1, U11.25 (IO0); also elsewhere on the board
ESP_RTS: U11.21 (SDO/SD0); also elsewhere on the board
ESP_RX: U11.27 (IO16); also elsewhere on the board
ESP_TDO: U11.23 (IO15); also elsewhere on the board
ESP_TX: U11.28 (IO17); also elsewhere on the board
FPGA_TDO: U11.14 (IO12); also elsewhere on the board
GND: C1.2, C2.2, U11.1 (GND), U11.15 (GND), U11.38 (GND), U11.PAD (GND); also elsewhere on the board
USB_TCK: U11.16 (IO13); also elsewhere on the board
USB_TMS: U11.13 (IO14); also elsewhere on the board

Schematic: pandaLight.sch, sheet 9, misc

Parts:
FID1, FID2, FID3, FID4, FID5, FID6, FID7, FID8: FIDUCIAL1X2; FIDUCIAL-1X2

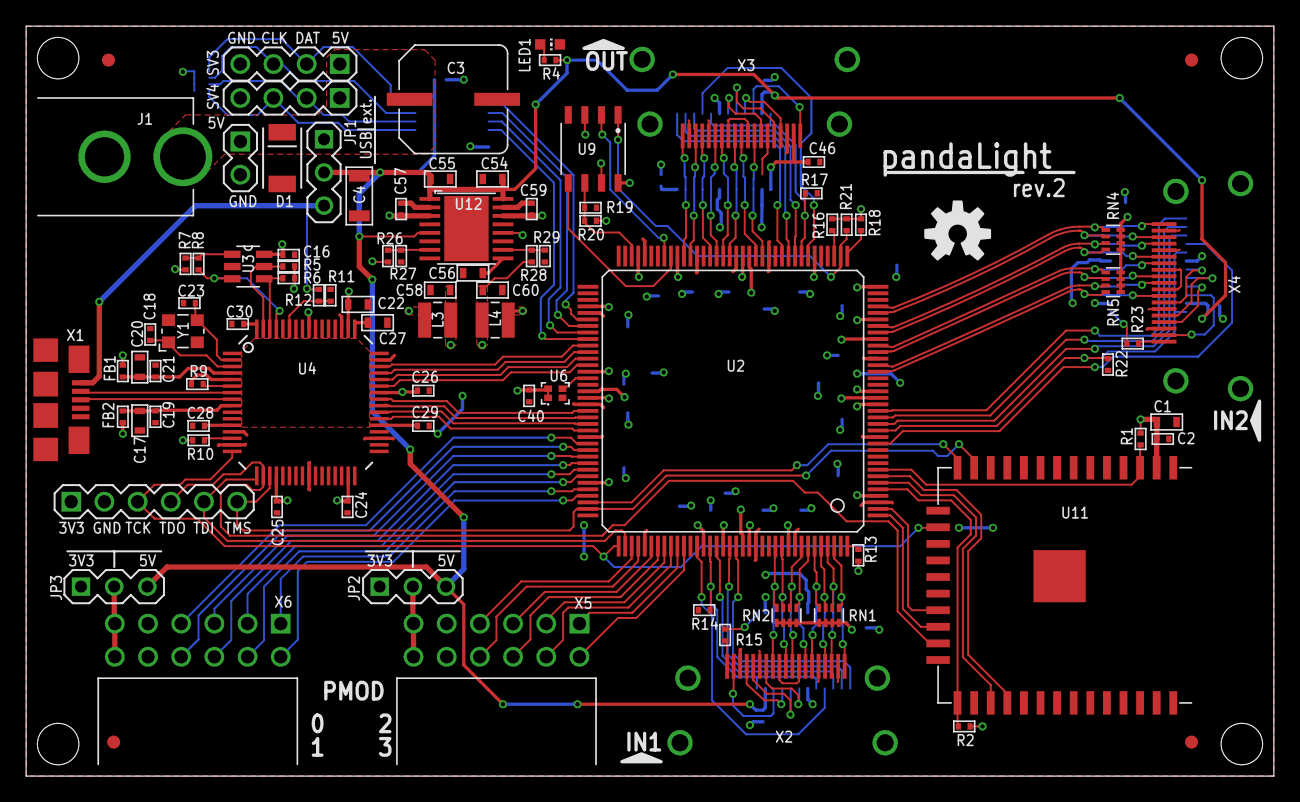
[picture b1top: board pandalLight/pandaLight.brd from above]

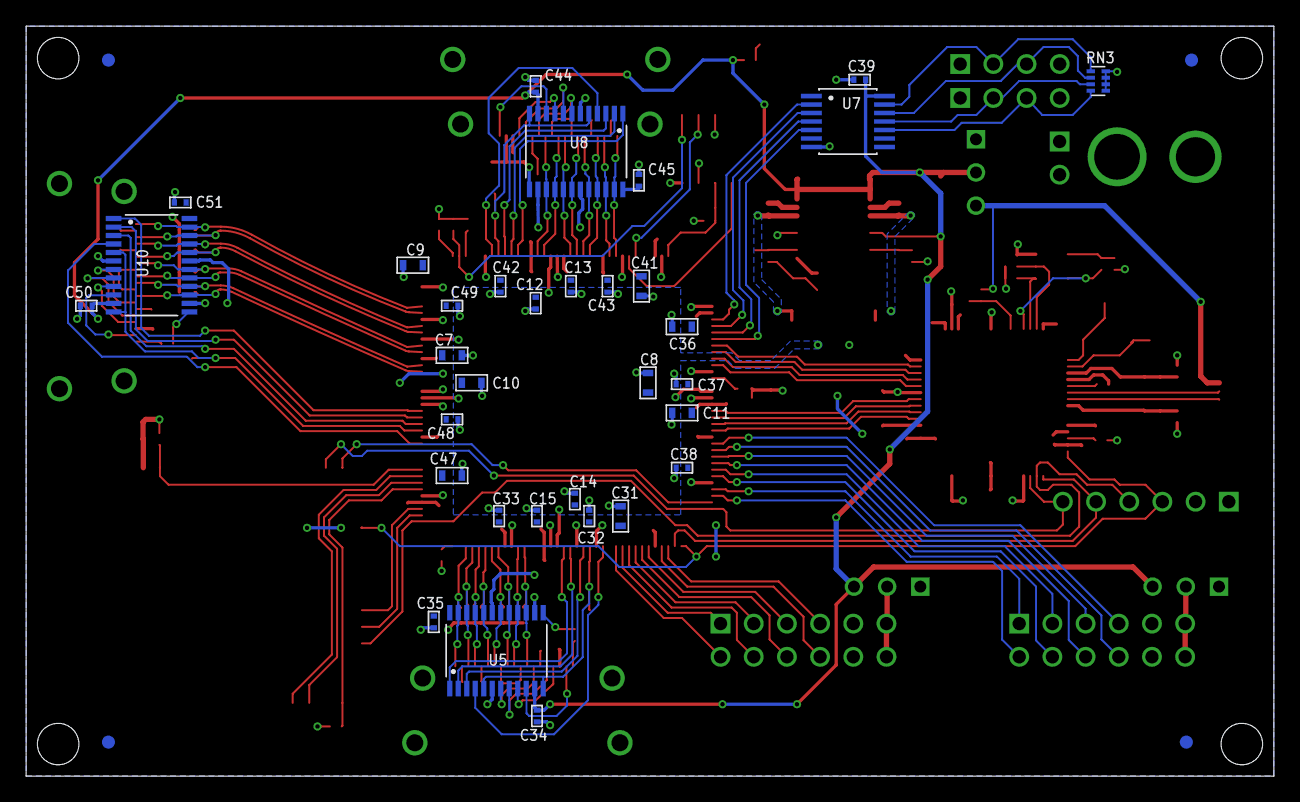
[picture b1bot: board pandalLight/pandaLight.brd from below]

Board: 2 copper layers, 95.5 x 57.4 mm, 128 parts (37 on the bottom side), 137 nets.

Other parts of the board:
OSHW-LOGO: OSHW-LOGO-M
